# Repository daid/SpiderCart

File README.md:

# SpiderCart

SpiderCart is a new gameboy and gameboy color flash cartridge. Which will have many legs over the alternatives.

Currently, it is still in development. But it uses a different setup compared to other flash carts. Other carts use FPGAs or CPLDs. Instead the SpiderCart uses a single RP2354B microcontroller to function as the MBC and handle all other functionalities required. This offers greater flexiblity at lower costs.

The SpiderCart is fully open source MIT license. And can be produced and copied by anyone. It also has all the flexibility to be modified by anyone.

## Terminology

This repository documents the technical side of the SpiderCart. Because of this it uses a lot of terminology. This list ensures that we all speak the same language.

* DMG: The origonal grey brick gameboy. With 4 "green" colors.
* GBC: The Gameboy Color. Upgraded version of the grey brick with color support, double CPU speed and a few more things.
* MCU: Microcontroller. In this case the RP2354B from Raspberry Pi. The RP2354B is a RP2350 with internal flash, so references to RP2350 are also refering to this chip.
* SRAM: "Save" ram. This is also called "external ram" from the gameboy perspective, and contained within the cartridge. Optionally this is preserved between power cycles. Not to be confused with "Static RAM" which is a name of a specific type of RAM chips (to which we just refer as RAM chip)
* RTC: A clock. The gameboy documentation usually refers to this as the Timer. It keep "clock"/"wall" time. Even when the gameboy is off. This requires a battery to preserve state.
* Firmware: Code installed on the MCU that facilitates the operation of the flash cart
* Loader: The code running on the gameboy that allows selecting of rom files and potentially do other things.

## Features

The following features are working:

* Support running DMG and GBC roms up to 2MB in size (V1 limitation, design supports up to 8MB)
* Saves backed up to SD card automatically
* Menu to load ROMs from SD card
* Directly loading ROMs through the USB port for quick ROM debugging/testing
* Optional quickboot to start a rom without resetting and running the bootrom (not compatible with all roms)

The following features are in development:

* Pico-8 support
* USB port direct access to SD card for easy file updating without taking out the SD card
* Full support for RTC (Harvest Moon / Pokemon / Homebrew)
* 3 axis accelerometer (Kirby's Tilt 'n' Tumble / Homebrew)
* Rumble support

The following features are ideas that could work but not actively being developed right now:

* Customizable loader to make rom selection look how you want it, current loader is ugly but functional
* SD file access for homebrew
* USB networking
* NES emulation
* Doom

## Implementation

The SpiderCart is implemented by connecting the MCU and RAM chip directly to the gameboy cartridge bus. The RAM chip is loaded with whatever ROM needs to run. The rom is loaded by the MCU into the RAM chip, this can be done while the gameboy is kept in reset.

While the gameboy is running, the MCU needs to act like the MBC, controlling when the RAM chip is enabled, as well as simulating the SRAM. It will only need of the two CPU cores this MCU has, so 1 will be available for other functionality.

On the 150Mhz RP2350 Core1 is constantly running as MBC, while core0 handles things like saving SRAM and communicating with the RTC/Accelerometer/USB.

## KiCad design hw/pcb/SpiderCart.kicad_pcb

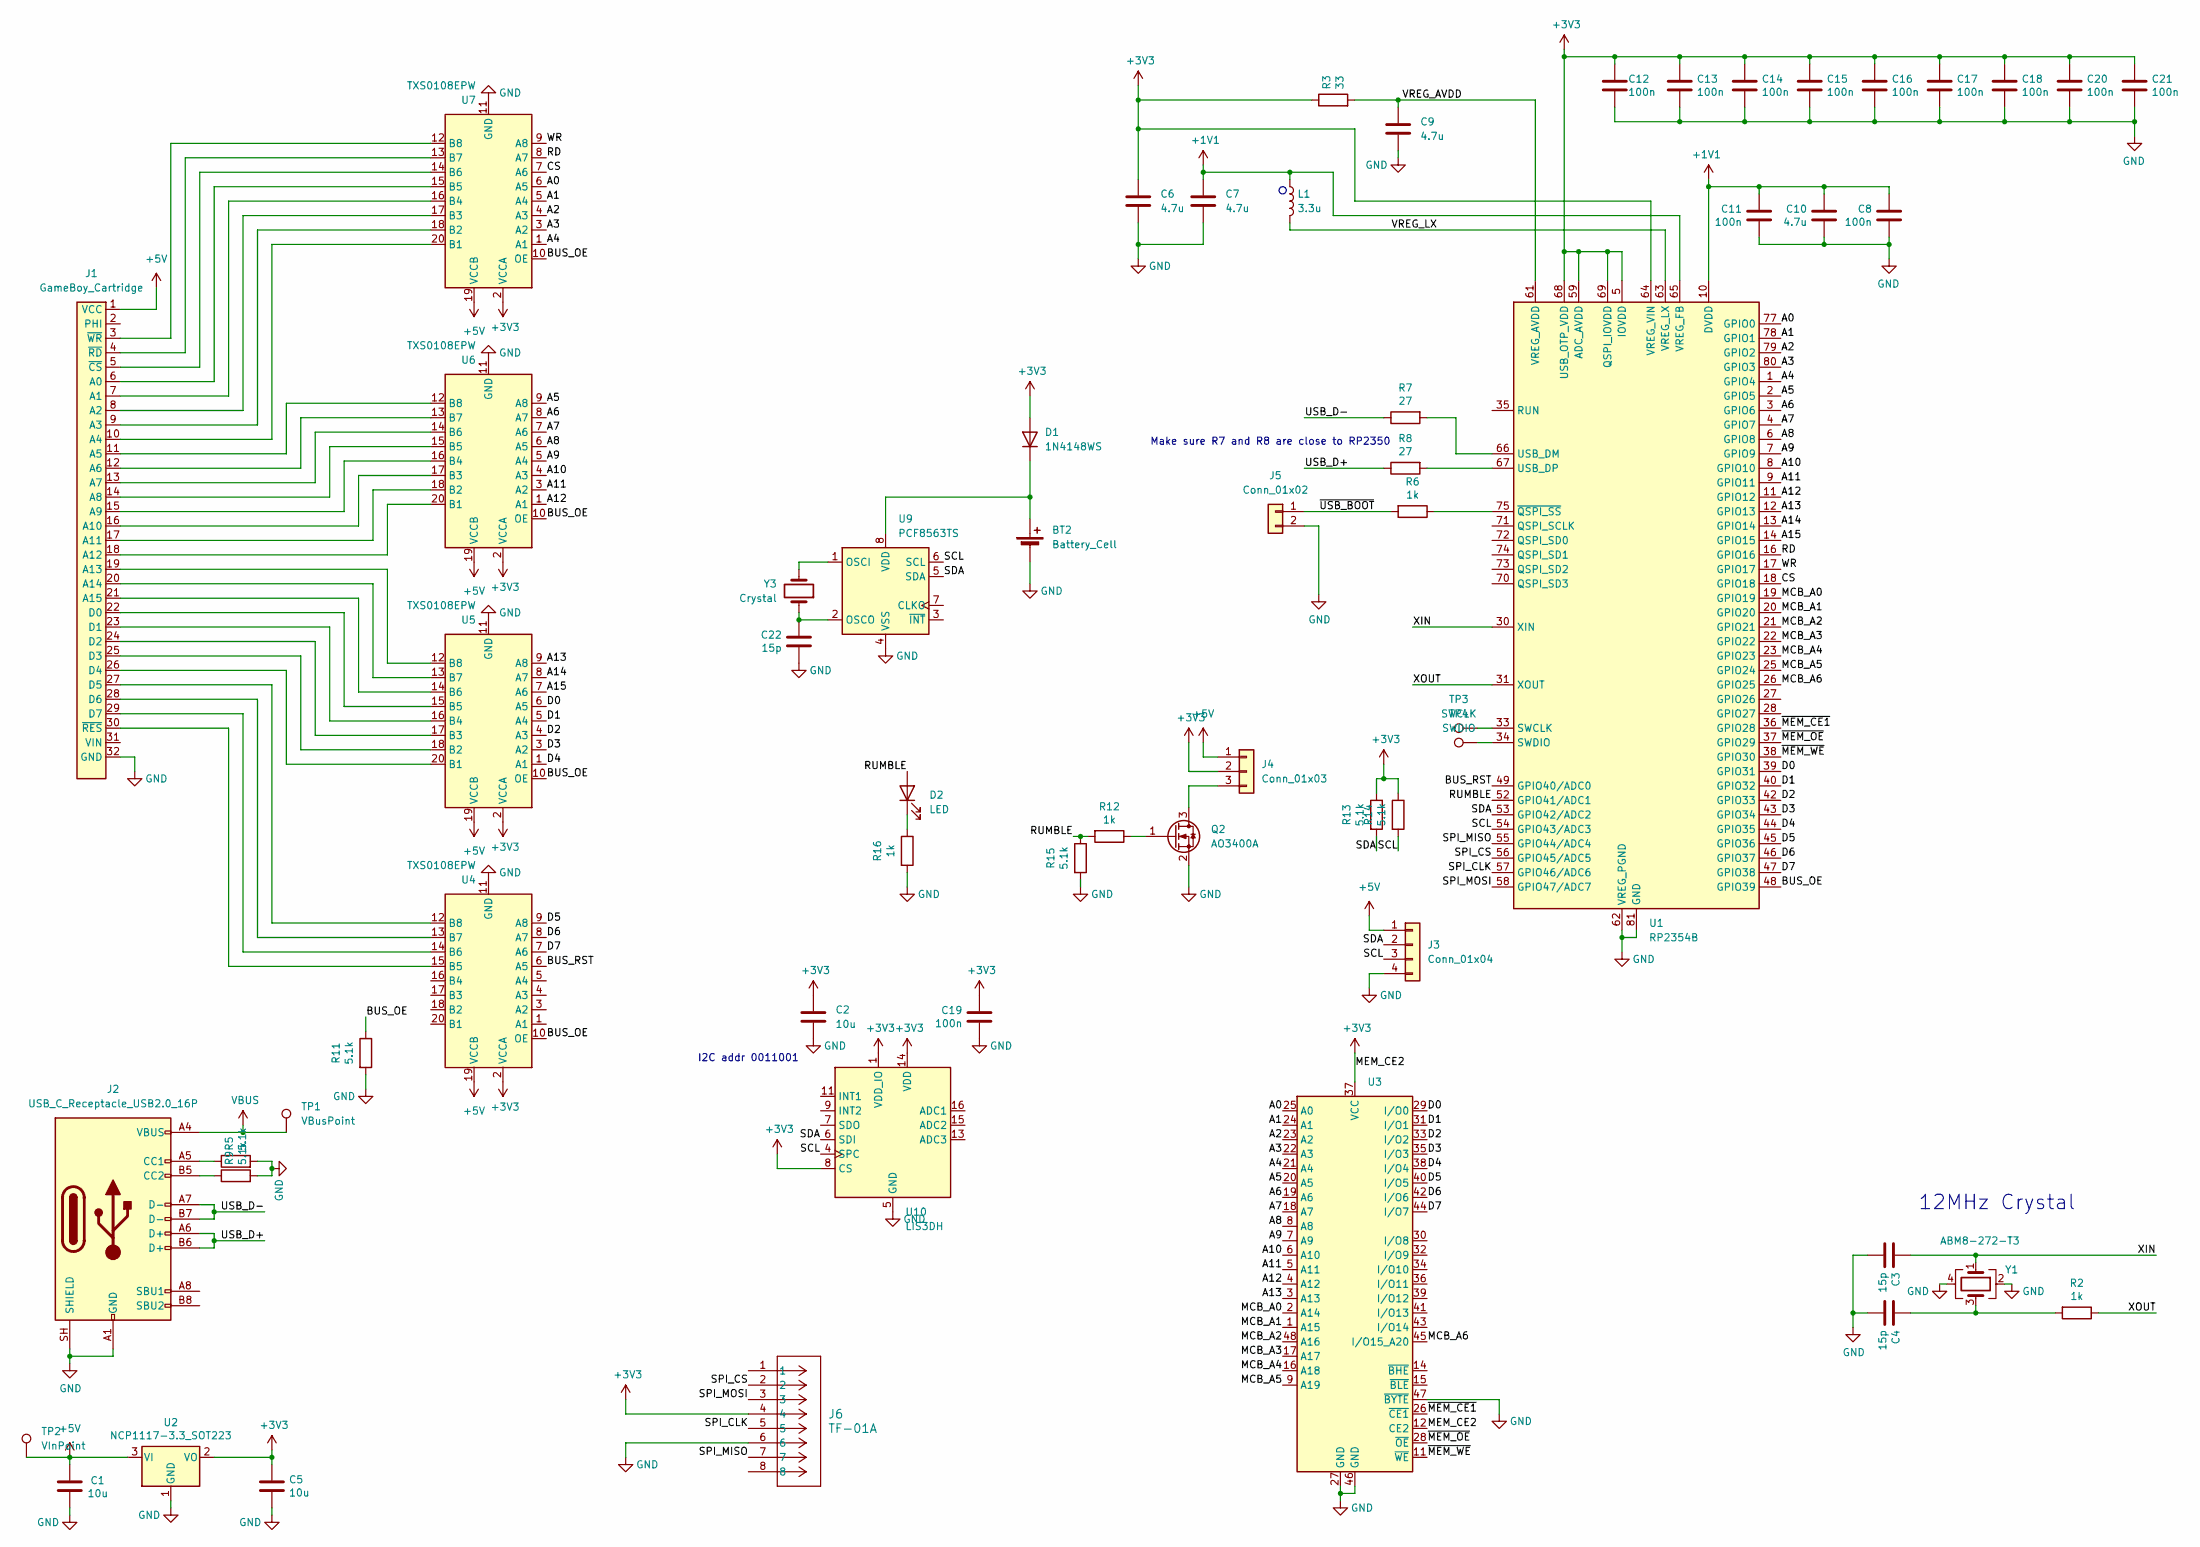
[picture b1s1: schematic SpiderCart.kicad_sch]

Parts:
BT2: Battery_Cell; BatteryHolder_Keystone_2998_1x6.8mm
C1, C5: 10u; C_0805_2012Metric
C2: 10u; C_0402_1005Metric
C3, C4, C22: 15p; C_0402_1005Metric
C6, C7: 4.7u; C_0402_1005Metric_small_pads
C8, C11, C12, C13, C14, C15, C16, C17, C18, C19, C20, C21: 100n; C_0402_1005Metric
C9, C10: 4.7u; C_0402_1005Metric
D1: 1N4148WS; D_SOD-323
D2: LED; LED_0603_1608Metric
J1: GameBoy_Cartridge; GameBoy_Cartridge_1x32_P1.50mm_Edge
J2: USB_C_Receptacle_USB2.0_16P; USB_C_Receptacle_JAE_DX07S016JA1R1500
J3: Conn_01x04; PinHeader_1x04_P1.27mm_Vertical
J4: Conn_01x03; PinHeader_1x03_P1.27mm_Vertical
J5: Conn_01x02; PinSocket_1x02_P1.27mm_Vertical
J6: TF-01A; CONN_TF-01A_HRO
L1: 3.3u; L_pol_2016
Q2: AO3400A; SOT-23
R2, R6, R12, R16: 1k; R_0402_1005Metric
R3: 33; R_0402_1005Metric
R5, R9, R11, R13, R14, R15: 5.1k; R_0402_1005Metric
R7, R8: 27; R_0402_1005Metric
TP1: VBusPoint; PinHeader_1x01_P1.27mm_Vertical
TP2: VInPoint; PinHeader_1x01_P1.27mm_Vertical
TP3: SWCLK; TestPoint_Pad_D1.5mm
TP4: SWDIO; TestPoint_Pad_D1.5mm
U1: RP2354B; QFN-80-1EP_10x10mm_P0.4mm_EP3.4x3.4mm_ThermalVias
U2: NCP1117-3.3_SOT223; SOT-223-3_TabPin2
U3: TSOP-I-48_18.4x12mm_P0.5mm
U4, U5, U6, U7: TXS0108EPW; TSSOP-20_4.4x6.5mm_P0.65mm
U9: PCF8563TS; MSOP-8_3x3mm_P0.65mm
U10: LIS3DH; LGA-16_3x3mm_P0.5mm_LayoutBorder3x5y
Y1: ABM8-272-T3; Crystal_SMD_3225-4Pin_3.2x2.5mm
Y3: Crystal; Crystal_SMD_3215-2Pin_3.2x1.5mm

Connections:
+1V1: C7.1, C8.1, C10.1, C11.1, L1.1, U1.10 (DVDD), U1.32 (DVDD), U1.51 (DVDD), U1.65 (VREG_FB)
+3V3: C2.1, C5.1, C6.1, C12.1, C13.1, C14.1, C15.1, C16.1, C17.1, C18.1, C19.1, C20.1, C21.1, D1.2 (A), J4.2, J6.4, R3.1, R13.1, R14.1, U1.5 (IOVDD), U1.15 (IOVDD), U1.24 (IOVDD), U1.29 (IOVDD), U1.41 (IOVDD), U1.50 (IOVDD), U1.59 (ADC_AVDD), U1.60 (IOVDD), U1.64 (VREG_VIN), U1.68 (USB_OTP_VDD), U1.69 (QSPI_IOVDD), U1.76 (IOVDD), U2.2 (VO), U3.12 (CE2), U3.37 (VCC), U4.2 (VCCA), U5.2 (VCCA), U6.2 (VCCA), U7.2 (VCCA), U10.1 (VDD_IO), U10.8 (CS), U10.14 (VDD)
+5V: C1.1, J1.1 (VCC), J3.1, J4.1, TP2.1 (1_1), U2.3 (VI), U4.19 (VCCB), U5.19 (VCCB), U6.19 (VCCB), U7.19 (VCCB)
/A0: U1.77 (GPIO0), U3.25 (A0), U7.6 (A5)
/A1: U1.78 (GPIO1), U3.24 (A1), U7.5 (A4)
/A2: U1.79 (GPIO2), U3.23 (A2), U7.4 (A3)
/A3: U1.80 (GPIO3), U3.22 (A3), U7.3 (A2)
/A4: U1.1 (GPIO4), U3.21 (A4), U7.1 (A1)
/A5: U1.2 (GPIO5), U3.20 (A5), U6.9 (A8)
/A6: U1.3 (GPIO6), U3.19 (A6), U6.8 (A7)
/A7: U1.4 (GPIO7), U3.18 (A7), U6.7 (A6)
/A8: U1.6 (GPIO8), U3.8 (A8), U6.6 (A5)
/A9: U1.7 (GPIO9), U3.7 (A9), U6.5 (A4)
/A10: U1.8 (GPIO10), U3.6 (A10), U6.4 (A3)
/A11: U1.9 (GPIO11), U3.5 (A11), U6.3 (A2)
/A12: U1.11 (GPIO12), U3.4 (A12), U6.1 (A1)
/A13: U1.12 (GPIO13), U3.3 (A13), U5.9 (A8)
/A14: U1.13 (GPIO14), U5.8 (A7)
/A15: U1.14 (GPIO15), U5.7 (A6)
/BUS_OE: R11.1, U1.48 (GPIO39), U4.10 (OE), U5.10 (OE), U6.10 (OE), U7.10 (OE)
/BUS_RST: U1.49 (GPIO40/ADC0), U4.6 (A5)
/CS: U1.18 (GPIO18), U7.7 (A6)
/D0: U1.39 (GPIO31), U3.29 (I/O0), U5.6 (A5)
/D1: U1.40 (GPIO32), U3.31 (I/O1), U5.5 (A4)
/D2: U1.42 (GPIO33), U3.33 (I/O2), U5.4 (A3)
/D3: U1.43 (GPIO34), U3.35 (I/O3), U5.3 (A2)
/D4: U1.44 (GPIO35), U3.38 (I/O4), U5.1 (A1)
/D5: U1.45 (GPIO36), U3.40 (I/O5), U4.9 (A8)
/D6: U1.46 (GPIO37), U3.42 (I/O6), U4.8 (A7)
/D7: U1.47 (GPIO38), U3.44 (I/O7), U4.7 (A6)
/MCB_A0: U1.19 (GPIO19), U3.2 (A14)
/MCB_A1: U1.20 (GPIO20), U3.1 (A15)
/MCB_A2: U1.21 (GPIO21), U3.48 (A16)
/MCB_A3: U1.22 (GPIO22), U3.17 (A17)
/MCB_A4: U1.23 (GPIO23), U3.16 (A18)
/MCB_A5: U1.25 (GPIO24), U3.9 (A19)
/MCB_A6: U1.26 (GPIO25), U3.45 (I/O15_A20)
/RD: U1.16 (GPIO16), U7.8 (A7)
/RUMBLE: D2.2 (A), R12.2, R15.1, U1.52 (GPIO41/ADC1)
/SCL: J3.3, R14.2, U1.54 (GPIO43/ADC3), U9.6 (SCL), U10.4 (SPC)
/SDA: J3.2, R13.2, U1.53 (GPIO42/ADC2), U9.5 (SDA), U10.6 (SDI)
/SPI_CLK: J6.5, U1.57 (GPIO46/ADC6)
/SPI_CS: J6.2, U1.56 (GPIO45/ADC5)
/SPI_MISO: J6.7, U1.55 (GPIO44/ADC4)
/SPI_MOSI: J6.3, U1.58 (GPIO47/ADC7)
/USB_D+: J2.A6 (D+), J2.B6 (D+), R8.1
/USB_D-: J2.A7 (D-), J2.B7 (D-), R7.1
/VREG_AVDD: C9.1, R3.2, U1.61 (VREG_AVDD)
/VREG_LX: L1.2, U1.63 (VREG_LX)
/WR: U1.17 (GPIO17), U7.9 (A8)
/XIN: C3.1, U1.30 (XIN), Y1.1
/XOUT: R2.1, U1.31 (XOUT)
/~MEM_CE1: U1.36 (GPIO28), U3.26 (~CE1)
/~MEM_OE: U1.37 (GPIO29), U3.28 (~OE)
/~MEM_WE: U1.38 (GPIO30), U3.11 (~WE)
/~USB_BOOT: J5.1, R6.2
GND: BT2.2 (-), C1.2, C2.2, C3.2, C4.2, C5.2, C6.2, C7.2, C8.2, C9.2, C10.2, C11.2, C12.2, C13.2, C14.2, C15.2, C16.2, C17.2, C18.2, C19.2, C20.2, C21.2, C22.2, J1.32 (GND), J2.A1 (GND), J2.A12 (GND), J2.B1 (GND), J2.B12 (GND), J2.SH (SHIELD), J3.4, J5.2, J6.6, Q2.2 (S), R5.2, R9.2, R11.2, R15.2, R16.2, U1.62 (VREG_PGND), U1.81 (GND), U2.1 (GND), U3.27 (GND), U3.46 (GND), U3.47 (~BYTE), U4.11 (GND), U5.11 (GND), U6.11 (GND), U7.11 (GND), U9.4 (VSS), U10.5 (GND), U10.10 (GND), U10.12 (GND), Y1.2, Y1.4
unnamed: BT2.1 (+), D1.1 (K), U9.8 (VDD)
unnamed: C4.1, R2.2, Y1.3
unnamed: D2.1 (K), R16.1
unnamed: J1.6 (A0), U7.15 (B5)
unnamed: J1.7 (A1), U7.16 (B4)
unnamed: J1.8 (A2), U7.17 (B3)
unnamed: J1.9 (A3), U7.18 (B2)
unnamed: J1.10 (A4), U7.20 (B1)
unnamed: J1.11 (A5), U6.12 (B8)
unnamed: J1.12 (A6), U6.13 (B7)
unnamed: J1.13 (A7), U6.14 (B6)
unnamed: J1.14 (A8), U6.15 (B5)
unnamed: J1.15 (A9), U6.16 (B4)
unnamed: J1.16 (A10), U6.17 (B3)
unnamed: J1.17 (A11), U6.18 (B2)
unnamed: J1.18 (A12), U6.20 (B1)
unnamed: J1.19 (A13), U5.12 (B8)
unnamed: J1.20 (A14), U5.13 (B7)
unnamed: J1.21 (A15), U5.14 (B6)
unnamed: J1.22 (D0), U5.15 (B5)
unnamed: J1.23 (D1), U5.16 (B4)
unnamed: J1.24 (D2), U5.17 (B3)
unnamed: J1.25 (D3), U5.18 (B2)
unnamed: J1.26 (D4), U5.20 (B1)
unnamed: J1.27 (D5), U4.12 (B8)
unnamed: J1.28 (D6), U4.13 (B7)
unnamed: J1.29 (D7), U4.14 (B6)
unnamed: J1.5 (~CS), U7.14 (B6)
unnamed: J1.4 (~RD), U7.13 (B7)
unnamed: J1.30 (~RES), U4.15 (B5)
unnamed: J1.3 (~WR), U7.12 (B8)
unnamed: J2.A5 (CC1), R5.1
unnamed: J2.B5 (CC2), R9.1
unnamed: J4.3, Q2.3 (D)
unnamed: Q2.1 (G), R12.1
unnamed: TP3.1 (1_1), U1.33 (SWCLK)
unnamed: TP4.1 (1_1), U1.34 (SWDIO)
unnamed: R7.2, U1.66 (USB_DM)
unnamed: R8.2, U1.67 (USB_DP)
unnamed: R6.1, U1.75 (~QSPI_SS)
unnamed: U9.1 (OSCI), Y3.2
unnamed: C22.1, U9.2 (OSCO), Y3.1
VBUS: J2.A4 (VBUS), J2.A9 (VBUS), J2.B4 (VBUS), J2.B9 (VBUS), TP1.1 (1_1)

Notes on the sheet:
12MHz Crystal
Make sure R7 and R8 are close to RP2350
I2C addr 0011001

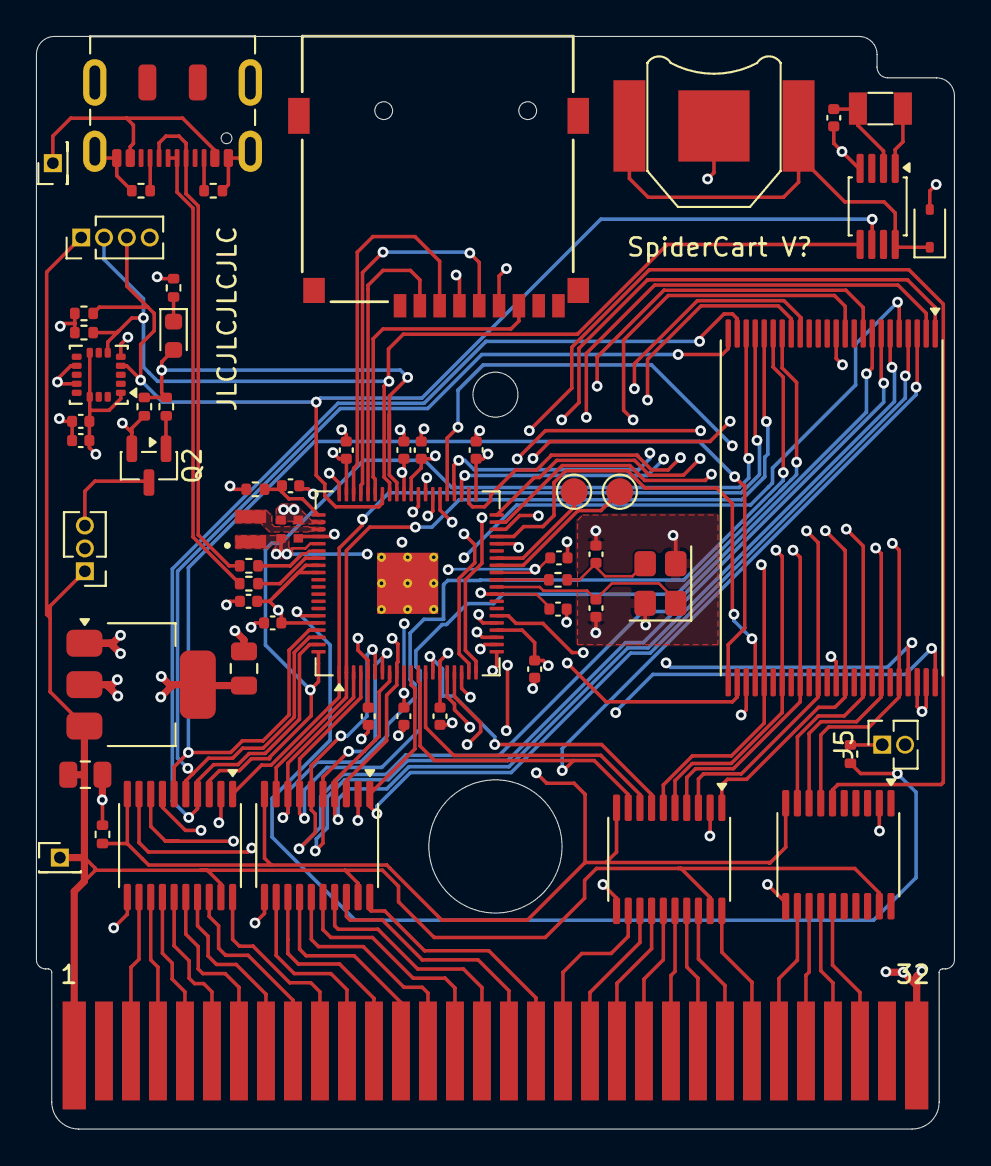
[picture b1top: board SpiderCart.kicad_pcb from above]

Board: 4 copper layers, 51.0 x 60.7 mm, 61 parts (0 on the bottom side), 100 nets.

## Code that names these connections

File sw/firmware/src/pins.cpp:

#include "pins.h"

#include "hardware/gpio.h"
#include "hardware/i2c.h"
#include "hardware/spi.h"
#include "hardware/pio.h"

#include "data_write.pio.h"
#include "data_read.pio.h"


void hwInit()
{
    gpio_init_mask(
        (0xFFFF << PIN_GB_A0) |
        (0x0001 << PIN_GB_RD) |
        (0x0001 << PIN_GB_WR) |
        (0x0001 << PIN_GB_CS) |
        (0x01FF << PIN_MBC_A0) |
        (0x0001 << PIN_MEM_CE) |
        (0x0001 << PIN_MEM_OE) |
        (0x0001 << PIN_MEM_WE)
    );
    gpio_set_dir_out_masked(
        (0x01FF << PIN_MBC_A0) |
        (0x0001 << PIN_MEM_CE) |
        (0x0001 << PIN_MEM_OE) |
        (0x0001 << PIN_MEM_WE)
    );
    gpio_put(PIN_MEM_CE, false);
    gpio_put(PIN_MEM_OE, true);
    gpio_put(PIN_MEM_WE, true);
    gpio_init(PIN_GB_D0);
    gpio_init(PIN_GB_D1);
    gpio_init(PIN_GB_D2);
    gpio_init(PIN_GB_D3);
    gpio_init(PIN_GB_D4);
    gpio_init(PIN_GB_D5);
    gpio_init(PIN_GB_D6);
    gpio_init(PIN_GB_D7);
    gpio_init(PIN_BUS_EN);
    gpio_set_dir(PIN_BUS_EN, true);
    gpio_put(PIN_BUS_EN, true);
    gpio_init(PIN_GB_RST);
    gpio_set_dir(PIN_GB_RST, true);
    gpio_put(PIN_GB_RST, false);
    gpio_init(PIN_RUMBLE);
    gpio_set_dir(PIN_RUMBLE, true);
    gpio_put(PIN_RUMBLE, false);

    i2c_init(i2c1, 100 * 1000);
    gpio_set_function(PIN_SDA, GPIO_FUNC_I2C);
    gpio_set_function(PIN_SCL, GPIO_FUNC_I2C);
    gpio_pull_up(PIN_SDA);
    gpio_pull_up(PIN_SCL);

    spi_init(spi1, 100 * 1000);
    spi_set_format(spi1, 8, SPI_CPOL_0, SPI_CPHA_0, SPI_MSB_FIRST);
    gpio_init(PIN_SD_CS);
    gpio_set_dir(PIN_SD_CS, true);
    gpio_put(PIN_SD_CS, true);
    gpio_set_function(PIN_SD_MISO, GPIO_FUNC_SPI);
    gpio_set_function(PIN_SD_CLK, GPIO_FUNC_SPI);
    gpio_set_function(PIN_SD_MOSI, GPIO_FUNC_SPI);
    gpio_pull_up(PIN_SD_MISO);

    // Configure pio0 for pins 16-47, and setup our pio programs to allow one cycle read/write of the data bus.
    pio_set_gpio_base(pio0, 16);
    hw_set_bits(&pio0->input_sync_bypass, 0xFF << (PIN_GB_D0 - 16));
    data_read_program_init(pio0, 1, pio_add_program(pio0, &data_read_program), PIN_GB_D0);
    data_write_program_init(pio0, 0, pio_add_program(pio0, &data_write_program), PIN_GB_D0);
}

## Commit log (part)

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2026-05-26 submodule update
2026-05-26 Add WIP SpiderCart electronics.
2026-05-26 Add I2C extension pins, and SWD pins
2026-05-27 readme update
2026-05-27 Add V1 text
2026-05-28 Update feature list.
2026-05-28 Add pin mapping
2026-05-28 Placeholder for where loader code will be.
2026-05-29 Check for GB.HLA installation.
2026-06-01 Better detect spidercart in emu.
2026-06-01 add template for firmware project
2026-06-06 i2c scan.
2026-06-06 More test code.
2026-06-06 Correct issues found in V1 production. I2C pullups where pulldowns, USB D- and D+ where swapped.
2026-06-09 small fixes on firmware, not fully tested yet.
2026-06-09 add test comms script
2026-06-09 Update shell model to fit the V1 PCB
2026-06-09 Fix MBC simulator not setting right pins
2026-06-09 Work towards quick data bus access (untested)
2026-06-10 Fix PIO programs for data bus read/write
2026-06-11 Full basic MBC implementation that should be good enough, untested.
2026-06-12 MBC emulation fix
2026-06-12 Fix SRAM read
2026-06-15 Reorganize bit of code.
2026-06-15 Improved cart case model.
2026-06-15 add command.h
2026-06-16 Start of a basic loader code
2026-06-16 add lua sources.
2026-06-16 Make lua 32 bit and add a few features found in pico8.
2026-06-16 Some work on pico8 lua support
2026-06-17 Add .gitignore
2026-06-17 Add hardware test firmware to validate if hardware works.
2026-06-17 Start working on disk IO
2026-06-18 WIP p8
2026-06-18 compile fatfs/diskio into firmware.
2026-06-18 Update GB.HLA build process
2026-06-18 Auto start Loader.gb
2026-06-18 Implemented shorthand if from z8lua.
2026-06-18 proper rng
2026-06-18 More functional p8 emulation.
2026-06-19 Various p8 fixes
2026-06-20 Actually load roms from SDCard
2026-06-20 Set the SPI frequency to 10mhz after SD initialization is complete to much faster load roms
2026-06-20 WIP quickboot.
2026-06-20 Quickboot with start and normal boot with A for now.
2026-06-20 Also set object palette when starting the loader
2026-06-20 Various p8 improvements.
2026-06-20 Change lua number parsing to allow for some pico8 oddness.
2026-06-20 Improve pico8 rendering.
2026-06-20 pico8 does not parse exponents
2026-06-20 Allow shorthand while.
2026-06-20 support pico8 int div operator
2026-06-20 Add support for %=
2026-06-20 more p8
2026-06-20 more p8 additions
2026-06-21 Start working on supporting different MBCs and save support
2026-06-21 Small p8 improvements.
2026-06-21 untested sav file saving (missing diskio part)
2026-06-21 Update on case model. untested SD write implementation
2026-06-22 Fix some compile warnings.
2026-06-22 More MBC support
2026-06-22 Make loader smaller by stripping it.
2026-06-22 Configure tinyusb custom, so we can add MSC later.
2026-06-22 Add disconnected USB storage device.
2026-06-22 Small P8 improvement. Small case update
2026-06-22 line placeholder for p8
2026-06-22 Put in the framework to support the RTC
2026-06-22 Add some serial debug commands to directly interface with sram.
2026-06-23 Fix SRAM write reliability issue.
2026-06-23 Make the loader tell what it is doing.
2026-06-23 Small improvements
2026-06-23 loader palette fix
2026-06-23 DMG seems to activate CS on WRAM access, so we need to check A14 as well when accessing SRAM
2026-06-23 Update case, update readme.
2026-06-23 Make USB inset in cartridge.
2026-06-23 p8 printh
2026-06-23 update p8 rom to work on DMG.
2026-06-24 Restructure the firmware a bit.
2026-06-24 update emulator to share code with the firmware.
2026-06-25 Compile fix
2026-06-25 Work towards pico8 on actual hardware
2026-06-25 new style compression
2026-06-25 prepare for better error reporting.
2026-06-26 Fix firmware compile
2026-06-26 Move emu into sw
2026-06-26 test
2026-06-26 different theme
2026-06-26 attempt at index page.
2026-06-26 placeholders
2026-06-26 WIP better error reporting.
2026-06-27 prepare for USB SD access.
2026-06-27 First run of pico8 on real gbc hardware.
2026-06-27 Add pico8 config menu
2026-06-27 Add support for some special chars and for short hand print.
2026-06-27 Add more constants.
2026-06-27 Implement &= and |= and some placeholder p8 functions.
2026-06-28 small p8 fixes
2026-06-30 update docs a bit
2026-06-30 Fix the wrong FET in V1 design
2026-06-30 start of hardware page
2026-06-30 Add coprocessor feature to enable/disable usb-msc to prevent dual-access to the SD card.
2026-06-30 Add more oops
